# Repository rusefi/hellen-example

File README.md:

# FAQ

Q: How do I get latest hellen-one?

A: ``.github/workflows/update-hellen-one-reference.yaml`` is set to pull latest hellen daily!

Q: I get error 'Cannot stat xx-yy__zz.kicad_pcb: No such file' but files are right there?

A: please do not use dashes and underscore symbols in file names.

Q: Automation says that aux_axis_origin is missing?

A: aux_axis_origin is required, please place it in the appropriate corner.

Q: I get "Cannot parse position" with negative value?

A: Please move origin point into left-bottom corner of the board since we cannot parse negative coordinates at the moment. See https://github.com/andreika-git/hellen-one/issues/349

Q: I am placing an order with JLCPCB and component orientation all looks wrong?!

A: See https://github.com/rusefi/uaefi/?tab=readme-ov-file#q-ive-place-an-order-with-jlcpcb-and-i-see-scary-looking-wrong-orientation

Q: What about firmware?

A: See https://github.com/rusefi/fw-custom-hellen144-f4 and https://github.com/rusefi/rusefi/wiki/Custom-Firmware

Q: Automation seems to work but files are not updated?

A: automation requires that you use default branch 'main'

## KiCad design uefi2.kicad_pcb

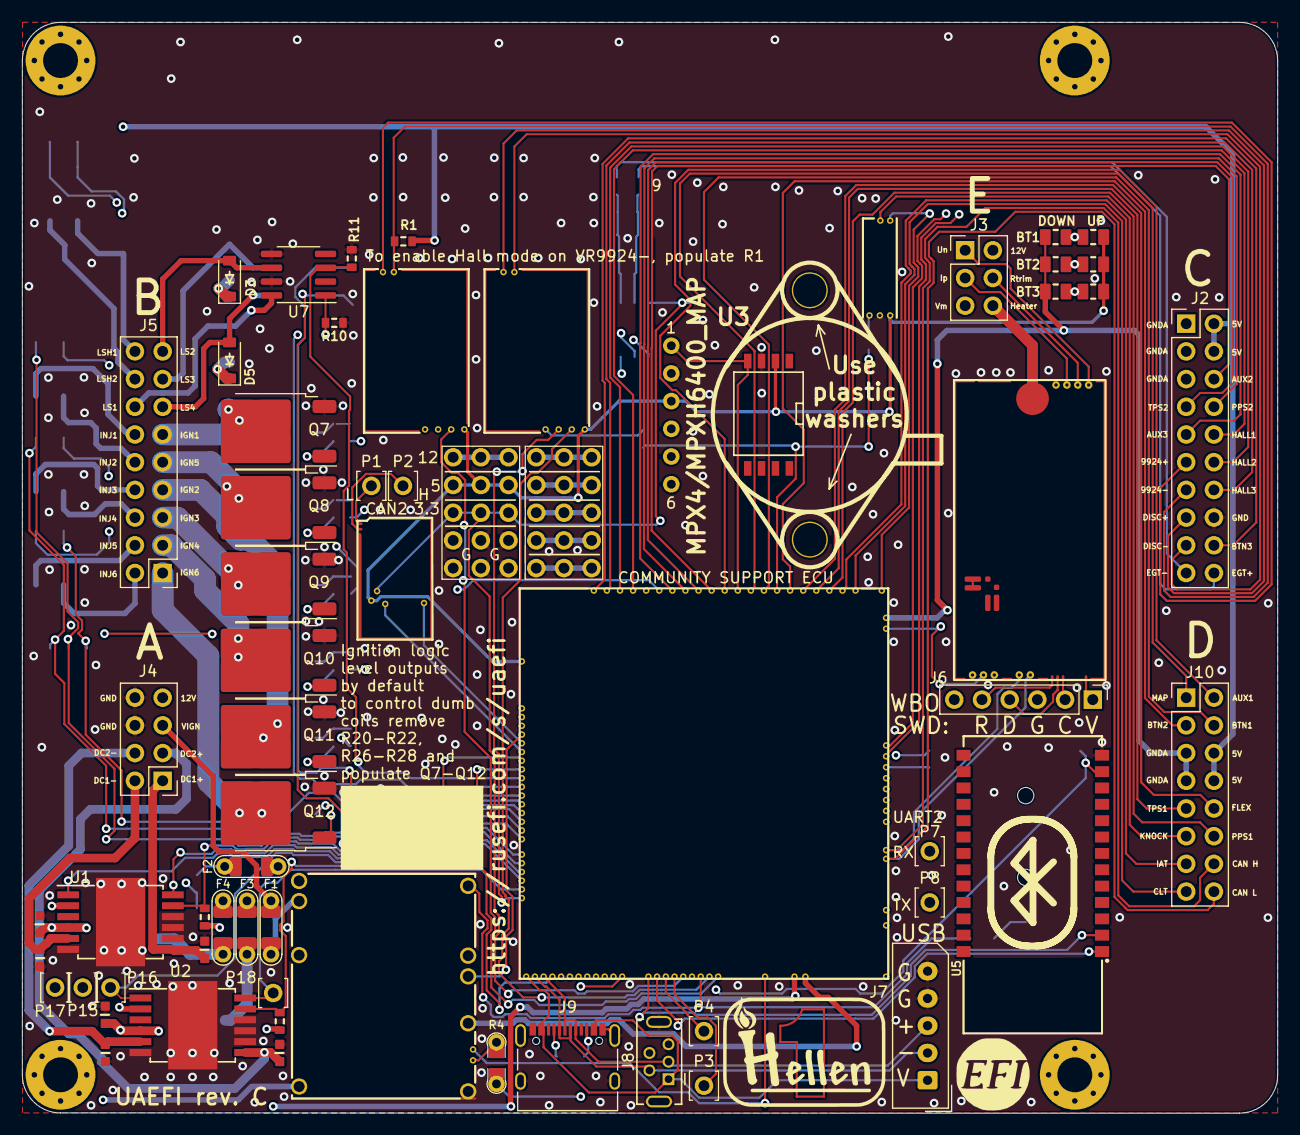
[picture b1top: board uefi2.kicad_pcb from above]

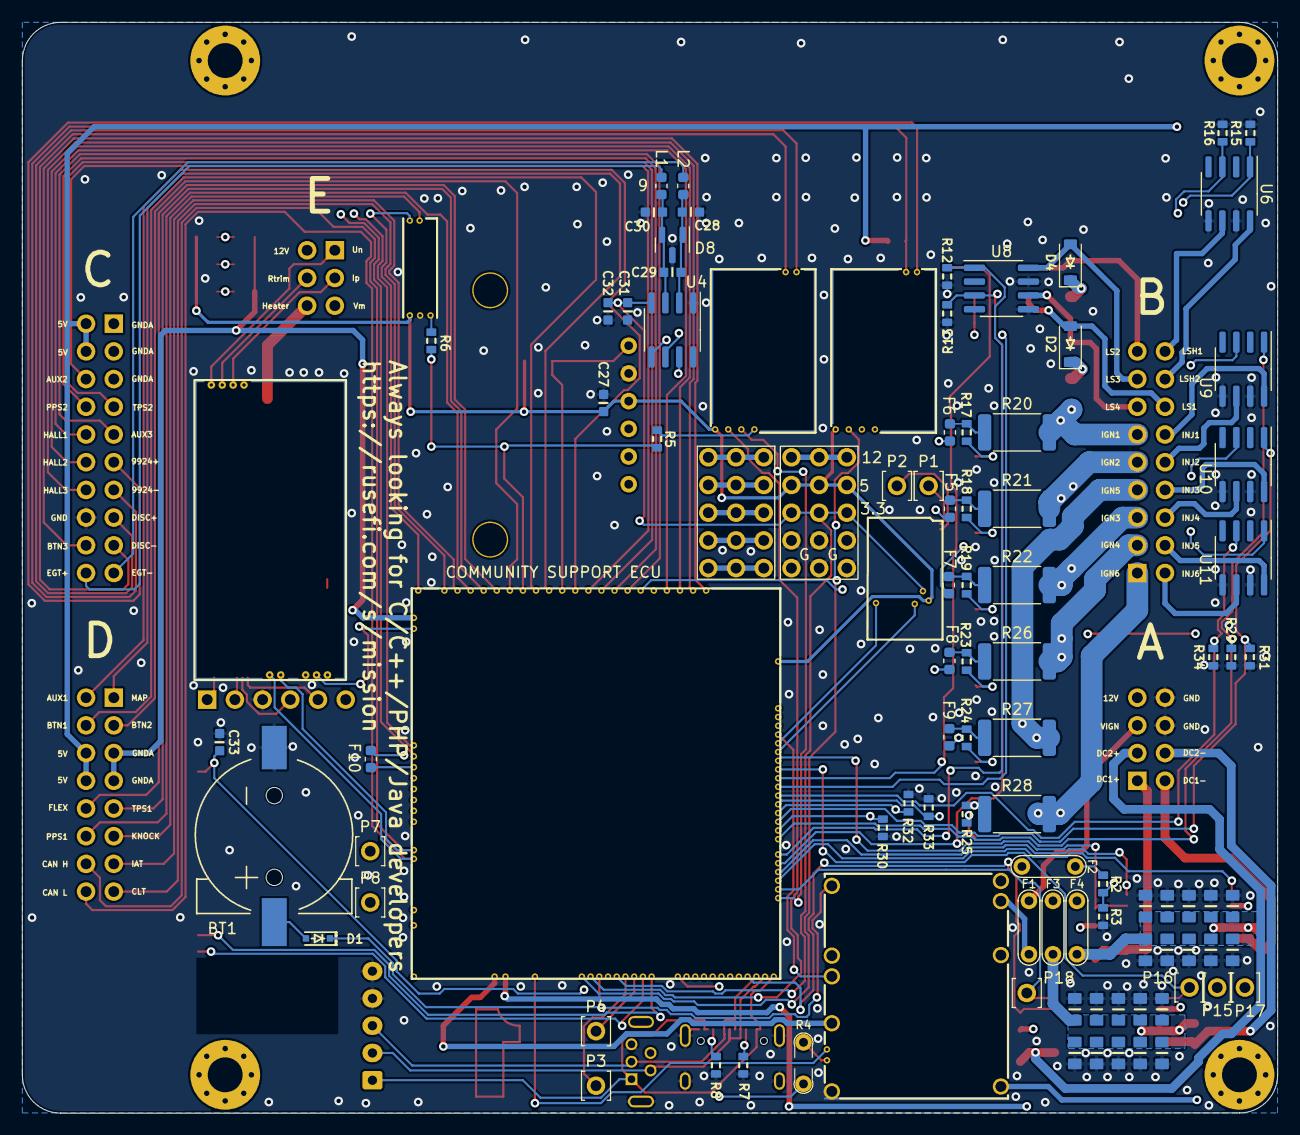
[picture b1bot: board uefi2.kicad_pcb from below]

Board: 4 copper layers, 115.1 x 100.0 mm, 143 parts (74 on the bottom side), 142 nets.

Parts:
BT1: CR1220; CR1220-2
C1, C2, C3, C4, C5, C6, C7, C8, C9, C10, C14, C15, C16, C17, C18, C19, C20, C21, C22, C23: 10u; C0805
C11, C24, C27, C29, C31, C33: 100n; C0603
C12, C13, C25, C26, C28, C30: 10n; C0603
C32: 1u; C0603
D1: 1N4148WS; SOD-323
D2, D3, D4, D5: B5819W; SOD-123
D8: NUP2105L; SOT-23
F1, F2, F3, F4: 12H1500D; PAD-1206-PAD
F5, F6, F7, F8, F9, F10: 50mA; Fuse_0603_1608Metric
G1: RUSEFI_LOGO; rusefi_logo
G2: LOGO
G3, G4: PROTO_AREA
H1, H2, H3, H4: M3; MountingHole_3.2mm_M3_Pad_Via
J2: Conn_02x10_Odd_Even; PinHeader_2x10_P2.54mm_Vertical
J3: Conn_02x03_Odd_Even; PinHeader_2x03_P2.54mm_Vertical
J4: Conn_02x04_Odd_Even; PinHeader_2x04_P2.54mm_Vertical
J5: Conn_02x09_Odd_Even; PinHeader_2x09_P2.54mm_Vertical
J6: Conn_01x06; PinHeader_1x06_P2.54mm_Vertical
J7: Conn_01x05_Male; Molex_SPOX_5267-05A_1x05_P2.50mm_Vertical
J8: USB_B_Mini; USB-MINI-B-VERTICAL
J9: USB_C
J10: Conn_02x08_Odd_Even; PinHeader_2x08_P2.54mm_Vertical
L1, L2: 470R@100MHz; L_0603_1608Metric
M1: Module-power_12and5V-0.2; power_12and5V
M2: Module-knock-0.2; knock
M3: Module-vr-discrete-0.5; vr-discrete
M4: Module-vr-max9924-0.1; vr-max9924
M5: Module-wbo-0.5; wbo
M6: Module:mega-mcu100/0.3; mega-mcu100
M7: Module-can-0.1; can
P1, P2, P3, P4, P7, P8, P15, P16, P17, P18: Pad; PAD-TH
Q7, Q8, Q9, Q10, Q11, Q12: ISL9V3040D3ST; TO-252-2
R1, R9, R10, R11, R12, R13, R14, R15, R16, R29, R30, R31, R32, R33, R34: 4.7k; R0603
R2: 33k; R0603
R3: 6.8k; R0603
R4: Jumper-Pad-Pad; PAD-0805-PAD
R5, R6: 0; R0603
R7, R8: 5.6k; R0603
R17, R18, R19, R23, R24, R25: 22; R0603
R20, R21, R22, R26, R27, R28: 0; R_2512_6332Metric
R35, R36, R37: 10k; R0805
R38, R39, R40: DNP; R0805
U1, U2: TLE9201SG; Infineon_PG-DSO-12-11
U3: MPX4/MPXH6400_MAP; MPX-4_MAP
U4: MAX31855KASA; SOIC-8_3.9x4.9mm_P1.27mm
U5: JDY-33
U6, U7, U8, U9, U10, U11: VNLD5160TR-E; SOIC-8_3.9x4.9mm_P1.27mm

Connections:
+3.3V: M6.N21 (V33), R9.2, R14.2, U1.2 (VSO), U2.2 (VSO)
+3.3VA: C31.2, C32.2, C33.2, G3.3, G3.8, G3.13, M6.N15 (V33_SWITCHABLE), M7.V2 (CAN_VIO), U4.4 (V_CC), U5.12 (3V3)
+5V: M1.E4 (V5), M6.N22 (VCC)
+5VA: C27.2, G3.4, G3.9, G3.14, M2.E1 (V5A), M3.E4 (V5_IN), M4.E4 (V5_IN), M5.W1 (V5_IN), M6.E1 (V5A_SWITCHABLE), M6.W2 (V5A_SWITCHABLE), M7.V1 (V5), R38.2, R39.2, R40.2, U3.3 (VCC)
+5VP: J2.2, J2.4, J10.6, J10.8, M1.V4 (5VP), R1.1
+12V: F2.1, F3.1, F4.1, J4.7, R2.2
+12V_RAW: D2.1 (K), D3.1 (K), D4.1 (K), D5.1 (K), F2.2, G3.5, G3.10, G3.15, J3.2, M1.V1 (V12_PERM), M1.V3 (V12_RAW)
/12V_KEY: F1.1, J4.5
/ADC3: M6.S15 (IN_KNOCK_(PA2)), R5.2, R6.2
/CAN+: J10.14, M5.W4 (CANH), M6.W11 (CANH)
/CAN-: J10.16, M5.W3 (CANL), M6.W12 (CANL)
/DC1_DIR: M6.E21 (OUT_PWM4_(PC8)), P15.1, U1.1 (DIR)
/DC1_DIS: M6.E8 (SPI2_MISO_(PB14)), R9.1, U1.11 (DIS)
/DC1_PWM: M6.E20 (OUT_PWM3_(PC7)), P17.1, U1.12 (PWM)
/DC2_DIR: M6.E9 (SPI2_MOSI_(PB15)), P16.1, U2.1 (DIR)
/DC2_DIS: M6.N4 (USBID_(PA10)), R14.1, U2.11 (DIS)
/DC2_PWM: M6.E22 (OUT_PWM5_(PC9)), P18.1, U2.12 (PWM)
/DC Driver 1/PWR: C1.2, C2.2, C3.2, C4.2, C5.2, C6.2, C7.2, C8.2, C9.2, C10.2, C11.2, U1.4 (VS)
/DC Driver 2/PWR: C14.2, C15.2, C16.2, C17.2, C18.2, C19.2, C20.2, C21.2, C22.2, C23.2, C24.2, U2.4 (VS)
/EGT+: J2.20, L1.1
/EGT-: J2.19, L2.1
/IGN1: F6.2, M6.W10 (IGN1_(PC13))
/IGN2: F5.2, M6.W9 (IGN2_(PE5))
/IGN3: F7.2, M6.W8 (IGN3_(PE4))
/IGN4: F8.2, M6.W7 (IGN4_(PE3))
/IGN5: F9.2, M6.W6 (IGN5_(PE2))
/IGN6: F10.2, M6.W5 (IGN6_(PB8))
/INJ1: M6.E17 (OUT_INJ1_(PD3)), R29.2, U9.1 (IN1)
/INJ2: M6.E16 (OUT_INJ2_(PA9)), R30.2, U9.3 (IN2)
/INJ3: M6.E15 (OUT_INJ3_(PD11)), R31.2, U10.1 (IN1)
/INJ4: M6.E14 (OUT_INJ4_(PD10)), R32.2, U10.3 (IN2)
/INJ5: M6.E13 (OUT_INJ5_(PD2)), R33.2, U11.1 (IN1)
/INJ6: M6.E12 (OUT_INJ6_(PA8)), R34.2, U11.3 (IN2)
/INTERNAL_MAP: M6.S12 (IN_MAP2_(PC1)), U3.1 (VOUT)
/IN_AUX1: J10.2, M6.S11 (IN_O2S_/_CAN_WAKEUP_(PA0))
/IN_AUX2: J2.6, M6.S10 (IN_O2S2_(PA1))
/IN_AUX3: J2.9, M6.S7 (IN_AUX3_(PA7))
/IN_BUTTON1: J10.4, M6.S14 (IN_CRANK_(PB1)), R35.2, R38.1
/IN_BUTTON2: J10.3, M6.S16 (IN_CAM_(PA6)), R36.2, R39.1
/IN_BUTTON3: J2.18, M6.S1 (IN_D4_(PE15)), R37.2, R40.1
/IN_CLT: J10.15, M6.S21 (IN_CLT_(PC2))
/IN_FLEX: J10.10, M6.S17 (IN_VSS_(PE11))
/IN_HALL1: J2.10, M6.S4 (IN_D1_(PE12))
/IN_HALL2: J2.12, M6.S3 (IN_D2_(PE13))
/IN_HALL3: J2.14, M6.S2 (IN_D3_(PE14))
/IN_IAT: J10.13, M6.S20 (IN_IAT_(PC3))
/IN_KNOCK: M2.E3 (OUT_KNOCK), R6.1
/IN_KNOCK_RAW: J10.11, M2.W1 (IN_KNOCK)
/IN_MAP: J10.1, M6.S13 (IN_MAP1_(PC0))
/IN_PPS1: J10.12, M6.S19 (IN_PPS_(PA3))
/IN_PPS2: J2.8, M6.S8 (IN_AUX2_(PC4/PE9))
/IN_TPS1: J10.9, M6.S18 (IN_TPS_(PA4))
/IN_TPS2: J2.7, M6.S9 (IN_AUX1_(PB0))
/IN_VIGN: F1.2, M1.V2 (IN_VIGN)
/IN_VMAIN: M6.S6 (IN_AUX4_(PC5)), R2.1, R3.2
/LS1: M6.E11 (OUT_INJ7_(PD15)), R10.2, U7.1 (IN1)
/LS2: M6.E10 (OUT_INJ8_(PD12)), R11.2, U7.3 (IN2)
/LS3: M6.E18 (OUT_PWM1_(PD13)), R12.2, U8.1 (IN1)
/LS4: M6.E19 (OUT_PWM2_(PC6)), R13.2, U8.3 (IN2)
/LS_HOT1: M6.W4 (IGN7_(PB9)), R16.1, U6.3 (IN2)
/LS_HOT2: M6.W3 (IGN8_(PE6)), R15.1, U6.1 (IN1)
/OUT_DC1+: C13.2, J4.1, U1.7 (OUT2)
/OUT_DC1-: C12.2, J4.2, U1.5 (OUT1)
/OUT_DC2+: C26.2, J4.3, U2.7 (OUT2)
/OUT_DC2-: C25.2, J4.4, U2.5 (OUT1)
/OUT_IGN1: J5.11, Q7.2 (C), R20.2
/OUT_IGN2: J5.9, Q8.2 (C), R21.2
/OUT_IGN3: J5.5, Q9.2 (C), R22.2
/OUT_IGN4: J5.3, Q10.2 (C), R26.2
/OUT_IGN5: J5.7, Q11.2 (C), R27.2
/OUT_IGN6: J5.1, Q12.2 (C), R28.2
/OUT_INJ1: J5.12, U9.8 (D1)
/OUT_INJ2: J5.10, U9.6 (D2)
/OUT_INJ3: J5.8, U10.8 (D1)
/OUT_INJ4: J5.6, U10.6 (D2)
/OUT_INJ5: J5.4, U11.8 (D1)
/OUT_INJ6: J5.2, U11.6 (D2)
/OUT_LS1: D2.2 (A), J5.14, U7.8 (D1)
/OUT_LS2: D3.2 (A), J5.17, U7.6 (D2)
/OUT_LS3: D4.2 (A), J5.15, U8.8 (D1)
/OUT_LS4: D5.2 (A), J5.13, U8.6 (D2)
/OUT_LS_HOT1: J5.18, U6.6 (D2)
/OUT_LS_HOT2: J5.16, U6.8 (D1)
/PG_5VP: M6.N12 (SPI3_MOSI_(PC12)), R4.2
/PWR_EN: M1.E5 (EN_5VP), M6.N20 (OUT_PWR_EN_(PE10))
/USB+: J7.3, J8.3 (D+), J9.A6 (D+), J9.B6 (D+), M6.N3 (USBP_(PA12))
/USB-: J7.2, J8.2 (D-), J9.A7 (D-), J9.B7 (D-), M6.N2 (USBM_(PA11))
/VBAT: D1.1 (K), M1.E1 (VBAT), M6.N17 (VBAT)
/VBUS: J7.1, J8.1 (VBUS), J9.A4 (VBUS), J9.A9 (VBUS), J9.B4 (VBUS), J9.B9 (VBUS), M6.N1 (VBUS)
/VIGN: M1.E3 (VIGN), M6.E5 (IN_VIGN_(PA5))
/VREF1: M2.W2 (VREF), M6.S22 (VREF1)
/VR_DISCRETE: M3.E3 (OUT), M6.N18 (UART8_RX_(PE0))
/VR_DISCRETE+: J2.15, M3.W2 (VR+)
/VR_DISCRETE-: J2.17, M3.W1 (VR-)
/VR_DISCRETE_A: M3.E2 (OUT_A), R5.1
/VR_DISCRETE_THR: M3.E1 (Thresh_IN), M6.E23 (OUT_PWM6_(PD14))
/VR_MAX9924: M4.E3 (OUT), M6.N19 (UART8_TX_(PE1))
/VR_MAX9924+: J2.11, M4.W2 (VR+)
/VR_MAX9924-: J2.13, M4.W1 (VR-), R1.2
/WBO_Heater: J3.6, M5.E5 (LSU_H+)
/WBO_Ip: J3.3, M5.E3 (LSU_Ip)
/WBO_Rtrim: J3.4, M5.E4 (LSU_Rtrim)
/WBO_Un: J3.1, M5.E1 (LSU_Un)
/WBO_Vm: J3.5, M5.E2 (LSU_Vm)
GND: BT1.2 (-), C1.1, C2.1, C3.1, C4.1, C5.1, C6.1, C7.1, C8.1, C9.1, C10.1, C11.1, C12.1, C13.1, C14.1, C15.1, C16.1, C17.1, C18.1, C19.1, C20.1, C21.1, C22.1, C23.1, C24.1, C25.1, C26.1, C27.1, C28.1, C30.1, C31.1, C32.1, C33.1, D8.3 (A), G3.1, G3.2, G3.6, G3.7, G3.11, G3.12, J2.16, J4.6, J4.8, J6.3, J7.4, J7.5, J8.5 (GND), J8.6 (Shield), J9.A1 (GND), J9.A12 (GND), J9.B1 (GND), J9.B12 (GND), J9.S1 (SHIELD), M1.S1 (GND), M2.E2 (GND), M3.G (GND), M4.G (GND), M5.E6 (LSU_H-), M5.G (GND), M6.G (GND), M7.E1 (GND), Q7.3 (E), Q8.3 (E), Q9.3 (E), Q10.3 (E), Q11.3 (E), Q12.3 (E), R3.1, R7.1, R8.1, R10.1, R11.1, R12.1, R13.1, R15.2, R16.2, R29.1, R30.1, R31.1, R32.1, R33.1, R34.1, U1.6 (GND), U1.8 (SI), U1.9 (CSN), U1.10 (SCK), U1.13 (GND), U2.6 (GND), U2.8 (SI), U2.9 (CSN), U2.10 (SCK), U2.13 (GND), U3.2 (GND), U4.1 (GND), U5.13 (GND), U6.5 (S2), U6.7 (S1), U7.5 (S2), U7.7 (S1), U8.5 (S2), U8.7 (S1), U9.5 (S2), U9.7 (S1), U10.5 (S2), U10.7 (S1), U11.5 (S2), U11.7 (S1)
GNDA: J2.1, J2.3, J2.5, J10.5, J10.7, M6.W1 (GNDA), R35.1, R36.1, R37.1
unnamed: BT1.1 (+), D1.2 (A)
unnamed: F5.1, R18.2, R21.1
unnamed: F6.1, R17.2, R20.1
unnamed: F7.1, R19.2, R22.1
unnamed: F8.1, R23.2, R26.1
unnamed: F9.1, R24.2, R27.1
unnamed: F10.1, R25.2, R28.1
unnamed: G4.1, G4.6, G4.11
unnamed: G4.5, G4.10, G4.15
unnamed: G4.2, G4.7, G4.12
unnamed: G4.3, G4.8, G4.13
unnamed: G4.4, G4.9, G4.14
unnamed: J6.1, M5.W8 (V33_OUT)
unnamed: J6.2, M5.W7 (SWCLK)
unnamed: J6.4, M5.W6 (SWDIO)
unnamed: J6.5, M5.W5 (nReset)
unnamed: J9.A5 (CC1), R7.2
unnamed: J9.B5 (CC2), R8.2
unnamed: M1.E6 (PG_5VP), R4.1
unnamed: M5.J1 (SEL1), M5.J_GND1 (PULL_DOWN1)
unnamed: M6.N14a (LED_GREEN), P4.1
unnamed: M6.N14b (LED_YELLOW), P3.1
unnamed: M6.E6 (SPI2_CS_/_CAN2_RX_(PB12)), M7.V6 (CAN_RX)
unnamed: M6.E7 (SPI2_SCK_/_CAN2_TX_(PB13)), M7.V5 (CAN_TX)
unnamed: M6.N14 (UART2_RX_(PD6)), P7.1, U5.1 (TXD)
unnamed: M6.N13 (UART2_TX_(PD5)), P8.1, U5.2 (RXD)
unnamed: M7.S2 (CANH), P2.1
unnamed: M7.S1 (CANL), P1.1
unnamed: Q7.1 (G), R17.1
unnamed: Q8.1 (G), R18.1
unnamed: Q9.1 (G), R19.1
unnamed: Q10.1 (G), R23.1
unnamed: Q11.1 (G), R24.1
unnamed: Q12.1 (G), R25.1
unnamed: C29.2, C30.2, D8.2 (K), L1.2, U4.3 (T+)
unnamed: C28.2, C29.1, D8.1 (K), L2.2, U4.2 (T-)

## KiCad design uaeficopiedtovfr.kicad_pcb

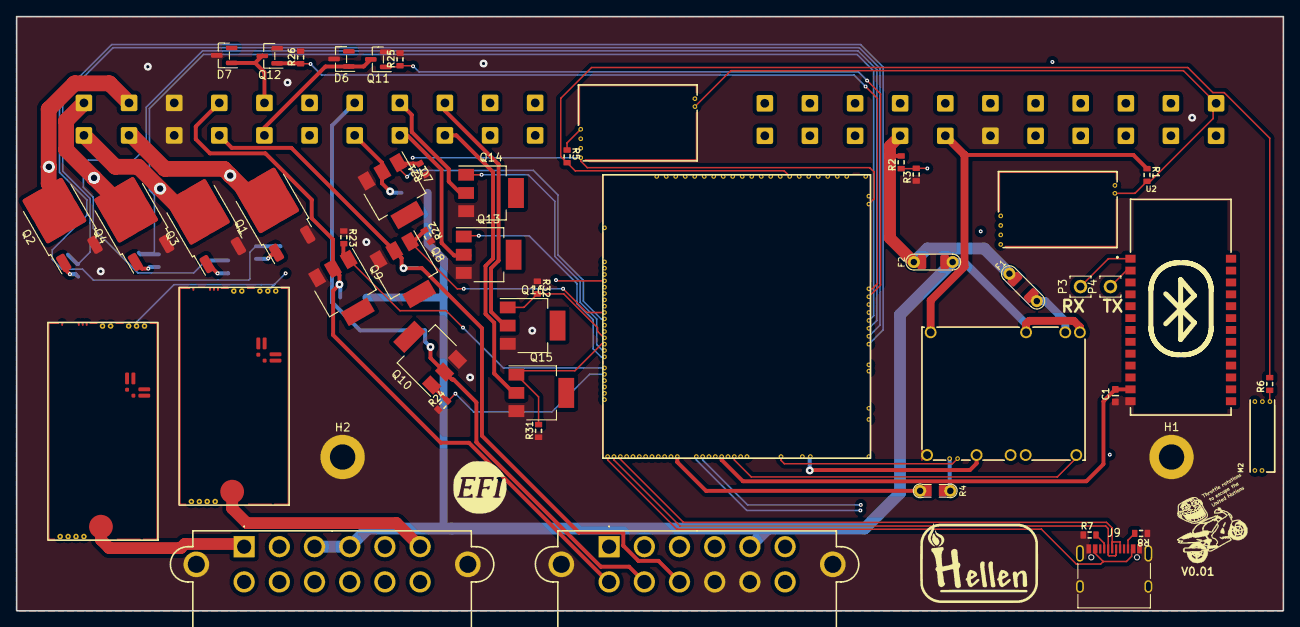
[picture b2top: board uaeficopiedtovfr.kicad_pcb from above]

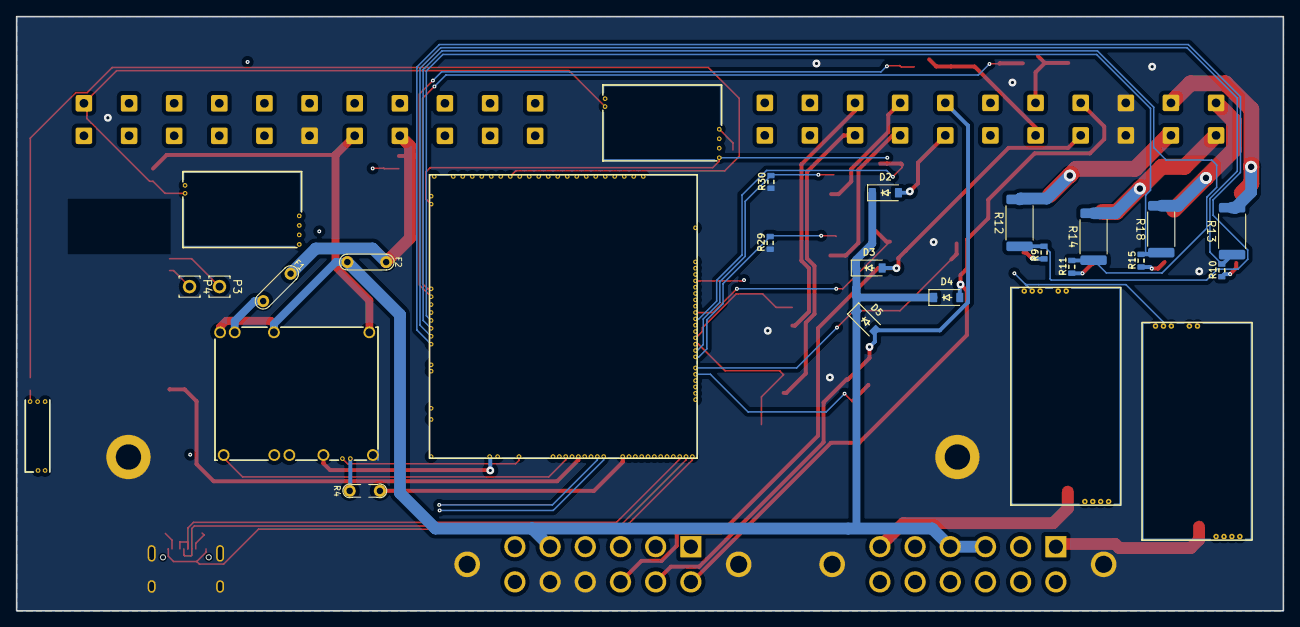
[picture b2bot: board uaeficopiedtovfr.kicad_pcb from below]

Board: 4 copper layers, 160.0 x 75.0 mm, 68 parts (14 on the bottom side), 85 nets.

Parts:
C1: 100n; C0603
D2, D3, D4, D5: B5819W; SOD-123
D6, D7: PSM712-LF; SOT-23
F1, F2: 12H1500D; PAD-1206-PAD
G3: RUSEFI_LOGO; rusefi_logo
G4: LOGO
H1, H2: MountingHole_Pad; MountingHole_3.2mm_M3_DIN965_Pad
J1, J4: DTF13-12PB; DTF1312PB
J9: USB_C_Receptacle_USB2.0; USB_C_Receptacle_XKB_U262-16XN-4BVC11
M1: Module-power_12and5V-0.2; power_12and5V
M2: Module-knock-0.2; knock
M3: Module-vr-discrete-0.4; vr-discrete
M4: Module-vr-max9924-0.1; vr-max9924
M5, M7: Module-wbo-0.5; wbo
M6: Module:mega-mcu100/0.2; mega-mcu100
P3, P4: Pad; PAD-TH
Q1, Q2, Q3, Q4: ISL9V3040D3S; TO-252-2
Q7, Q8, Q9, Q10, Q13, Q14, Q15, Q16: ZXMS6005SGTA; SOT-223
Q11, Q12: AO3400A; SOT-23
R1, R21, R22, R23, R24, R25, R26, R29, R30, R31, R32: 4.7k; R0603
R2: 33k; R0603
R3: 6.8k; R0603
R4: Jumper-Pad-Pad; PAD-0805-PAD
R5, R6: 0; R0603
R7, R8: 5.6k; R0603
R9, R10, R11, R15: 22; R0603
R12, R13, R14, R18: 0; R_2512_6332Metric
U1: VFRboardempty
U2: JDY-33
text1: trollfaceVFR

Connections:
+3.3VA: C1.2, M6.N15 (V33_SWITCHABLE), U2.12 (3V3)
+5V: M1.E4 (V5), M6.N22 (VCC)
+5VA: M2.E1 (V5A), M3.E4 (V5_IN), M4.E4 (V5_IN), M5.W1 (V5_IN), M6.E1 (V5A_SWITCHABLE), M6.W2 (V5A_SWITCHABLE), M7.W1 (V5_IN)
+5VP: M1.V4 (5VP), R1.1, U1.B7
+12V: F1.1, F2.1, R2.2, U1.B8
+12V_RAW: D2.1 (K), D3.1 (K), D4.1 (K), D5.1 (K), F2.2, J1.3, J1.4, J4.5, M1.V1 (V12_PERM), M1.V3 (V12_RAW)
/ADC3: M6.S15 (IN_KNOCK_(PA2)), R5.2, R6.2
/BARO: M6.S7 (IN_AUX3_(PC5)), U1.B4
/CAM+: M3.W2 (VR+), U1.B11
/CAM/CRANK-: M3.W1 (VR-), M4.W1 (VR-), R1.2, U1.B12
/CAN+: J4.7, M5.W4 (CANH), M6.W11 (CANH), M7.W4 (CANH)
/CAN-: J4.6, M5.W3 (CANL), M6.W12 (CANL), M7.W3 (CANL)
/CLT: M6.S21 (IN_CLT_(PC2)), U1.B15
/CRANK+: M4.W2 (VR+), U1.B22
/FILIGHT: D6.1, Q11.2 (D), U1.A7
/FUELPUMP_LS: D2.2 (A), Q7.2 (D), U1.A5
/IAT_SENSOR: M6.S20 (IN_IAT_(PC3)), U1.B5
/IGN1: M6.W10 (IGN1_(PC13)), R9.2, R12.1
/IGN2: M6.W9 (IGN2_(PE5)), R10.2, R13.1
/IGN3: M6.W8 (IGN3_(PE4)), R11.2, R14.1
/IGN4: M6.W7 (IGN4_(PE3)), R15.2, R18.1
/IGNOUT1: Q1.2 (C), R12.2, U1.A10
/IGNOUT2: Q2.2 (C), R13.2, U1.A21
/IGNOUT3: Q3.2 (C), R14.2, U1.A11
/IGNOUT4: Q4.2 (C), R18.2, U1.A22
/INJ1: M6.E17 (OUT_INJ1_(PD3)), Q13.1 (G), R29.2
/INJ2: M6.E16 (OUT_INJ2_(PA9)), Q14.1 (G), R30.2
/INJ3: M6.E15 (OUT_INJ3_(PD11)), Q15.1 (G), R31.2
/INJ4: M6.E14 (OUT_INJ4_(PD10)), Q16.1 (G), R32.2
/INJOUT1: Q13.2 (D), U1.A4
/INJOUT2: Q14.2 (D), U1.A15
/INJOUT3: Q15.2 (D), U1.A3
/INJOUT4: Q16.2 (D), U1.A14
/INTAKEFLAP: D5.2 (A), J4.11, Q10.2 (D), U1.A16
/IN_FLEX: J4.3, M6.S17 (IN_VSS_(PE11))
/IN_KNOCK: M2.E3 (OUT_KNOCK), R6.1
/IN_KNOCK_RAW: J4.4, M2.W1 (IN_KNOCK)
/IN_MAP: M6.S13 (IN_MAP1_(PC0)), U1.B3
/IN_TPS1: M6.S18 (IN_TPS_(PA4)), U1.B14
/IN_VIGN: F1.2, M1.V2 (IN_VIGN)
/IN_VMAIN: M6.S6 (IN_AUX4_(PA7)), R2.1, R3.2
/LS1: M6.E11 (OUT_INJ7_(PD15)), Q7.1 (G), R21.2
/LS2: M6.E10 (OUT_INJ8_(PD12)), Q8.1 (G), R22.2
/LS3: M6.E18 (OUT_PWM1_(PD13)), Q9.1 (G), R23.2
/LS4: M6.E19 (OUT_PWM2_(PC6)), Q10.1 (G), R24.2
/LS_WEAK1: M6.W4 (IGN7_(PB9)), Q11.1 (G), R25.1
/LS_WEAK2: M6.W3 (IGN8_(PE6)), Q12.1 (G), R26.1
/OUT_LS2: D3.2 (A), J4.10, Q8.2 (D), U1.A8
/OUT_LS3: D4.2 (A), J4.12, Q9.2 (D), U1.A19
/OUT_LS_WEAK2: D7.1, Q12.2 (D), U1.A18
/PG_5VP: M6.N12 (SPI3_MOSI_(PC12)), R4.2
/PWR_EN: M1.E5 (EN_5VP), M6.N20 (OUT_PWR_EN_(PE10))
/USB+: J9.A6 (D+), J9.B6 (D+), M6.N3 (USBP_(PA12))
/USB-: J9.A7 (D-), J9.B7 (D-), M6.N2 (USBM_(PA11))
/VBAT: M1.E1 (VBAT), M6.N17 (VBAT)
/VBUS: J9.A4 (VBUS), J9.A9 (VBUS), J9.B4 (VBUS), J9.B9 (VBUS), M6.N1 (VBUS)
/VIGN: M1.E3 (VIGN), M6.E5 (IN_VIGN_(PA5))
/VR1: M3.E3 (OUT), M6.N18 (UART8_RX_(PE0))
/VR1_A: M3.E2 (OUT_A), R5.1
/VR1_THRESHOLD: M3.E1 (Thresh_IN), M6.E23 (OUT_PWM6_(PD14))
/VR2: M4.E3 (OUT), M6.N19 (UART8_TX_(PE1))
/VREF1: M2.W2 (VREF), M6.S22 (VREF1)
/WBO2_Heater: J1.1, M7.E5 (LSU_H+)
/WBO2_Ip: J1.11, M7.E3 (LSU_Ip)
/WBO2_Rtrim: J1.2, M7.E4 (LSU_Rtrim)
/WBO2_Un: J1.10, M7.E1 (LSU_Un)
/WBO2_Vm: J1.12, M7.E2 (LSU_Vm)
/WBO_Heater: J1.6, M5.E5 (LSU_H+)
/WBO_Ip: J1.8, M5.E3 (LSU_Ip)
/WBO_Rtrim: J1.5, M5.E4 (LSU_Rtrim)
/WBO_Un: J1.9, M5.E1 (LSU_Un)
/WBO_Vm: J1.7, M5.E2 (LSU_Vm)
GND: C1.1, D6.2, D7.2, H1.1, H2.1, J1.MH1, J1.MH2, J4.8, J4.9, J4.MH1, J4.MH2, J9.A1 (GND), J9.A12 (GND), J9.B1 (GND), J9.B12 (GND), J9.S1 (SHIELD), M1.S1 (GND), M2.E2 (GND), M3.G (GND), M4.G (GND), M5.E6 (LSU_H-), M5.G (GND), M6.G (GND), M7.E6 (LSU_H-), M7.G (GND), Q1.3 (E), Q2.3 (E), Q3.3 (E), Q4.3 (E), Q7.3 (S), Q8.3 (S), Q9.3 (S), Q10.3 (S), Q11.3 (S), Q12.3 (S), Q13.3 (S), Q14.3 (S), Q15.3 (S), Q16.3 (S), R3.1, R7.1, R8.1, R21.1, R22.1, R23.1, R24.1, R25.2, R26.2, R29.1, R30.1, R31.1, R32.1, U1.A9, U1.A20, U1.B6, U2.13 (GND)
GNDA: M6.W1 (GNDA), U1.B2
unnamed: J9.A5 (CC1), R7.2
unnamed: J9.B5 (CC2), R8.2
unnamed: M1.E6 (PG_5VP), R4.1
unnamed: M5.J1 (SEL1), M5.J_GND1 (PULL_DOWN1)
unnamed: M6.N14 (UART2_RX_(PD6)), P3.1, U2.1 (TXD)
unnamed: M6.N13 (UART2_TX_(PD5)), P4.1, U2.2 (RXD)
unnamed: M7.J1 (SEL1), M7.J_GND1 (PULL_DOWN1)
unnamed: Q1.1 (G), R9.1
unnamed: Q2.1 (G), R10.1
unnamed: Q3.1 (G), R11.1
unnamed: Q4.1 (G), R15.1

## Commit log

2023-12-28 created 4 layer version
2023-12-28 Redesigned board to use 4 layers
    module files are 4 layers, pointless to have the base board only be two
2023-12-28 Generate new board
2024-03-06 GHA says update hellen-one
2024-03-15 GHA says update kicad6-libraries
2024-10-04 attempt
2024-10-07 attempt2
